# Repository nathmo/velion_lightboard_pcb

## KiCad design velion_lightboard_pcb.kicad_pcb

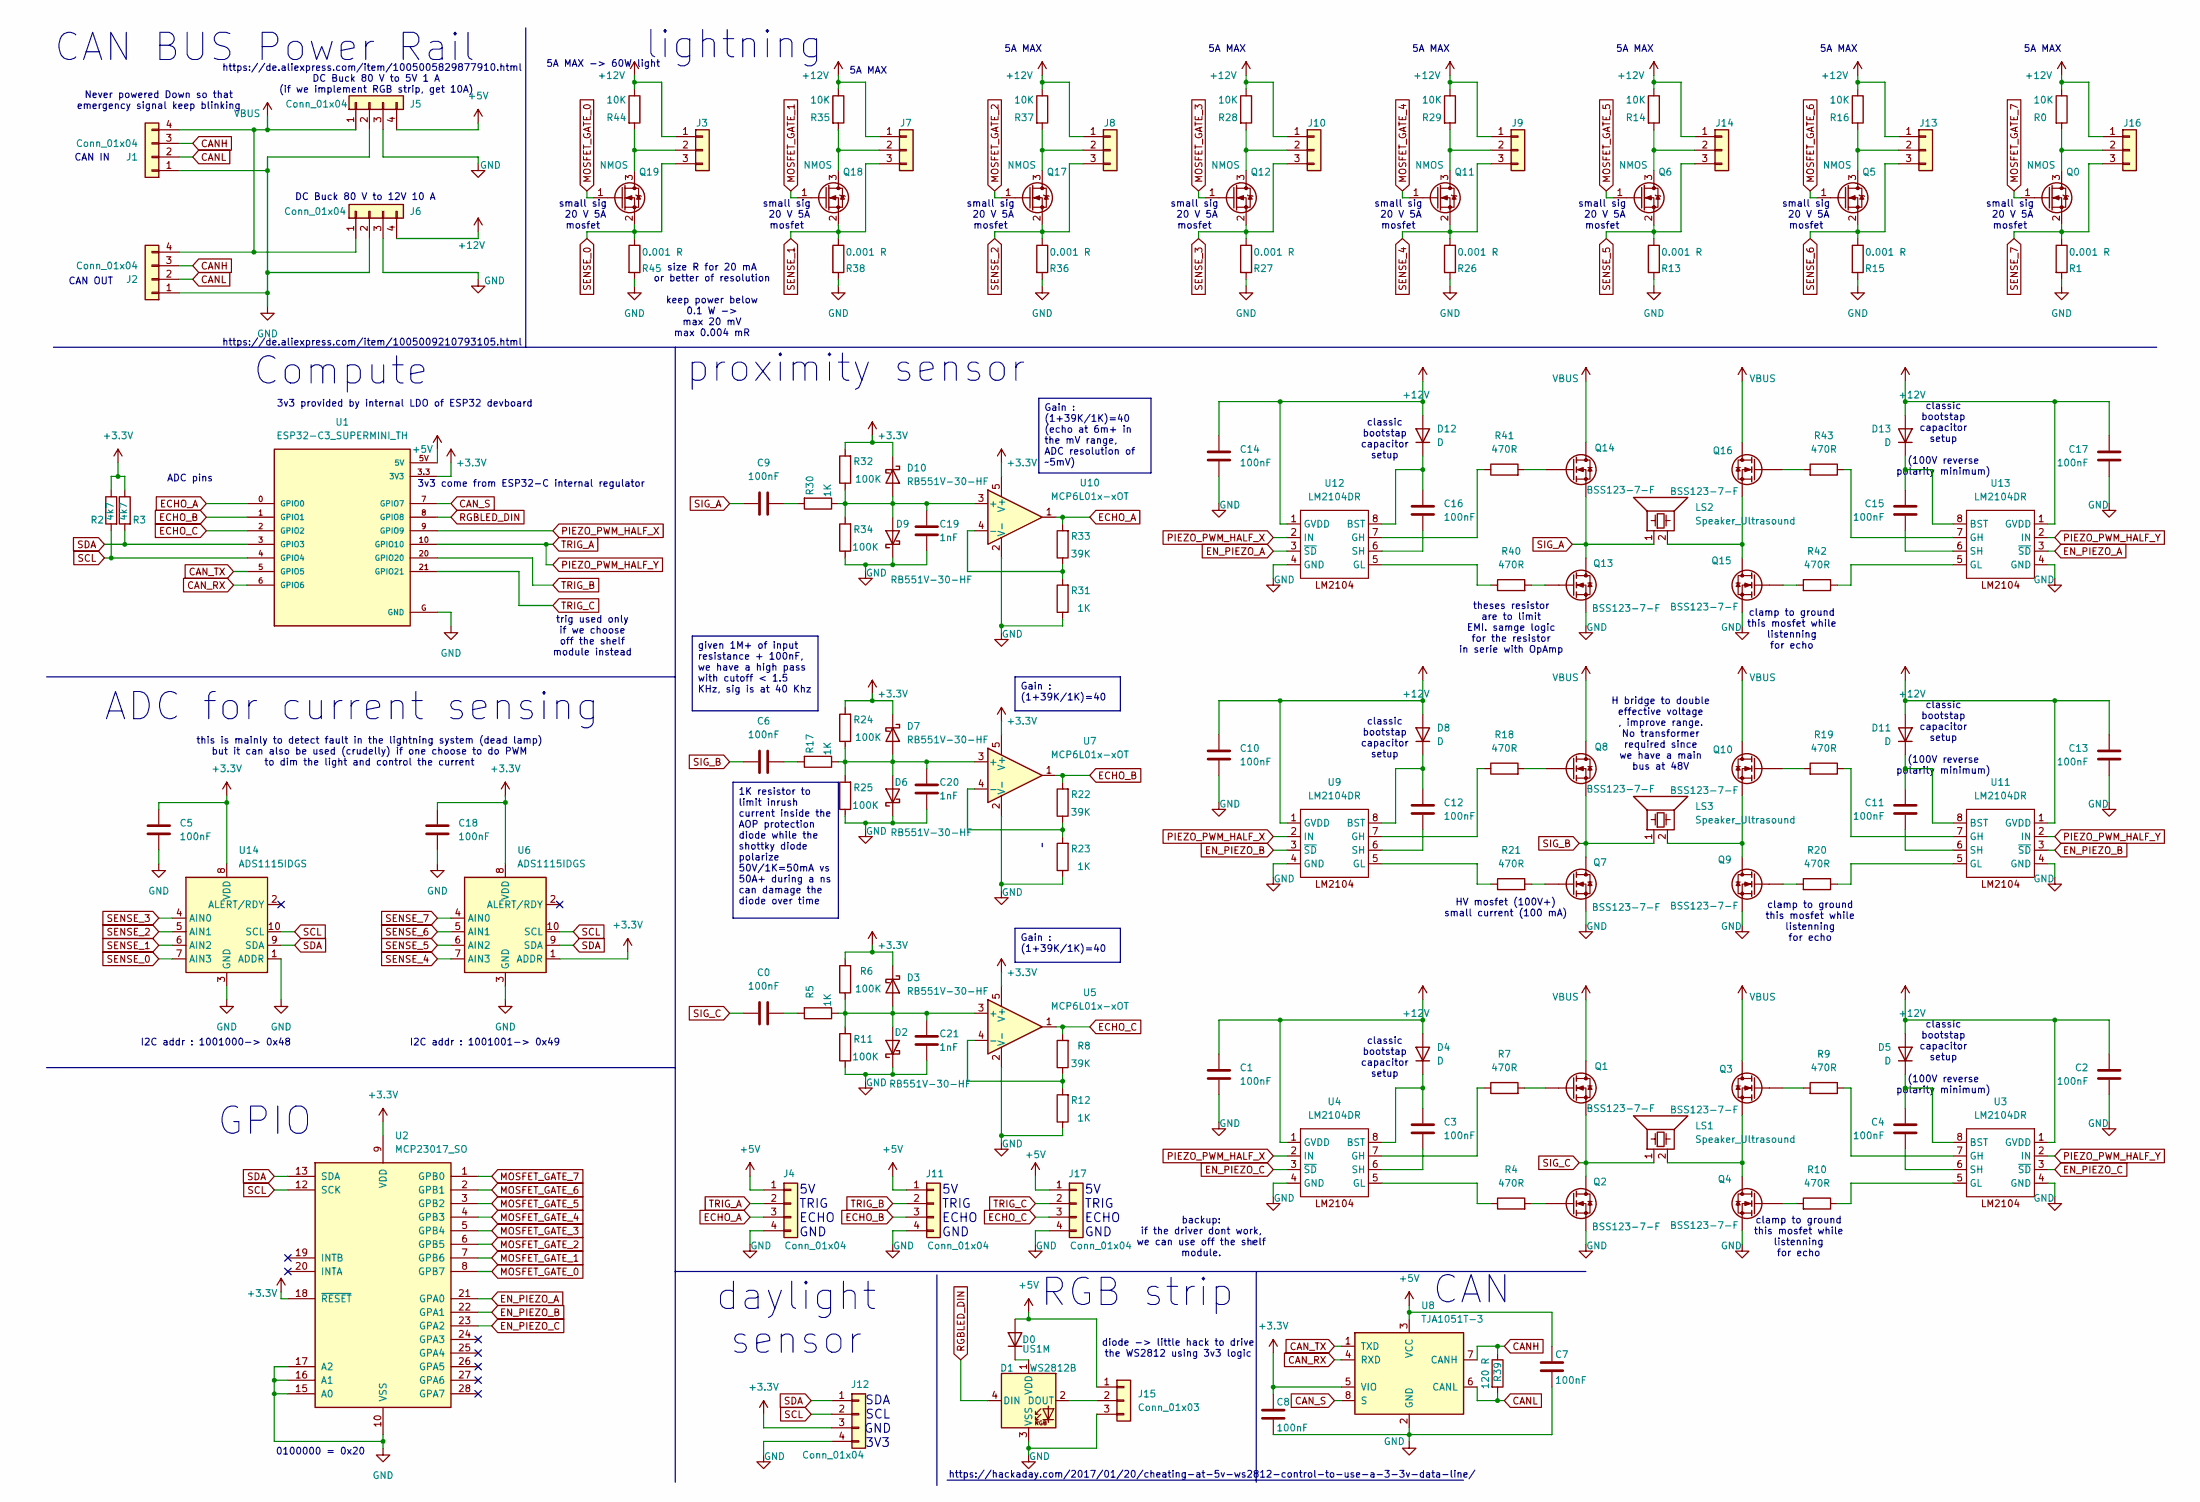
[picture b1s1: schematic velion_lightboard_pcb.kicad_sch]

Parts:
C0, C1, C2, C3, C4, C5, C6, C7, C8, C9, C10, C11, C12, C13, C14, C15, C16, C17, C18: 100nF; C_1206_3216Metric_Pad1.33x1.80mm_HandSolder
C19, C20, C21: 1nF; C_1206_3216Metric_Pad1.33x1.80mm_HandSolder
D0: US1M; D_SMA
D1: WS2812B; LED_WS2812B_PLCC4_5.0x5.0mm_P3.2mm
D2, D3, D6, D7, D9, D10: RB551V-30-HF; D_SOD-323_HandSoldering
D4, D5, D8, D11, D12, D13: D; D_SMA
J1, J2, J5, J6, J12: Conn_01x04; 15EDG-4P
J3, J7, J8, J9, J10, J13, J14, J15, J16: Conn_01x03; 15EDG-3P
J4, J11, J17: Conn_01x04; PinHeader_1x04_P2.54mm_Vertical
LS1, LS2, LS3: Speaker_Ultrasound; 15EDG-2P
Q0, Q5, Q6, Q11, Q12, Q17, Q18, Q19: NMOS; SOT-23
Q1, Q2, Q3, Q4, Q7, Q8, Q9, Q10, Q13, Q14, Q15, Q16: BSS123-7-F; BSS123_TSOT-23_HandSoldering
R0, R14, R16, R28, R29, R35, R37, R44: 10K; R_1206_3216Metric_Pad1.30x1.75mm_HandSolder
R1, R13, R15, R26, R27, R36, R38, R45: 0.001 R; R_2512_6332Metric_Pad1.40x3.35mm_HandSolder
R2, R3: 4k7; R_1206_3216Metric_Pad1.30x1.75mm_HandSolder
R4, R7, R9, R10, R18, R19, R20, R21, R40, R41, R42, R43: 470R; R_1206_3216Metric_Pad1.30x1.75mm_HandSolder
R5, R12, R17, R23, R30, R31: 1K; R_1206_3216Metric_Pad1.30x1.75mm_HandSolder
R6, R11, R24, R25, R32, R34: 100K; R_1206_3216Metric_Pad1.30x1.75mm_HandSolder
R8, R22, R33: 39K; R_1206_3216Metric_Pad1.30x1.75mm_HandSolder
R39: 120 R; R_1206_3216Metric_Pad1.30x1.75mm_HandSolder
U1: ESP32-C3_SUPERMINI_TH; MODULE_ESP32-C3_SUPERMINI_TH
U2: MCP23017_SO; SOIC-28W_7.5x17.9mm_P1.27mm
U3, U4, U9, U11, U12, U13: LM2104DR; SO-8_3.9x4.9mm_P1.27mm
U5, U7, U10: MCP6L01x-xOT; SOT-23-5
U6, U14: ADS1115IDGS; VSSOP-10_3x3mm_P0.5mm
U8: TJA1051T-3; SOIC-8_3.9x4.9mm_P1.27mm

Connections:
+3.3V: C5.1, C8.1, C18.1, D3.1 (K), D7.1 (K), D10.1 (K), J12.3, R2.1, R3.1, R6.2, R24.2, R32.2, U1.3.3 (3V3), U2.9 (VDD), U2.18 (~RESET), U5.5 (V+), U6.1 (ADDR), U6.8 (VDD), U7.5 (V+), U8.5 (VIO), U10.5 (V+), U14.8 (VDD)
+5V: C7.1, D0.2 (A), J4.1, J5.4, J11.1, J15.1, J17.1, U1.5V, U8.3 (VCC)
+12V: C1.1, C2.1, C10.1, C13.1, C14.1, C17.1, D4.2 (A), D5.2 (A), D8.2 (A), D11.2 (A), D12.2 (A), D13.2 (A), J3.1, J6.4, J7.1, J8.1, J9.1, J10.1, J13.1, J14.1, J16.1, R0.1, R14.1, R16.1, R28.1, R29.1, R35.1, R37.1, R44.1, U3.1 (GVDD), U4.1 (GVDD), U9.1 (GVDD), U11.1 (GVDD), U12.1 (GVDD), U13.1 (GVDD)
CANH: J1.3, J2.3, R39.1, U8.7 (CANH)
CANL: J1.2, J2.2, R39.2, U8.6 (CANL)
CAN_RX: U1.6 (GPIO6), U8.4 (RXD)
CAN_S: U1.7 (GPIO7), U8.8 (S)
CAN_TX: U1.5 (GPIO5), U8.1 (TXD)
ECHO_A: J4.3, R33.2, U1.0 (GPIO0), U10.1
ECHO_B: J11.3, R22.2, U1.1 (GPIO1), U7.1
ECHO_C: J17.3, R8.2, U1.2 (GPIO2), U5.1
EN_PIEZO_A: U2.21 (GPA0), U12.3 (~SD), U13.3 (~SD)
EN_PIEZO_B: U2.22 (GPA1), U9.3 (~SD), U11.3 (~SD)
EN_PIEZO_C: U2.23 (GPA2), U3.3 (~SD), U4.3 (~SD)
GND: C1.2, C2.2, C5.2, C7.2, C8.2, C10.2, C13.2, C14.2, C17.2, C18.2, C19.1, C20.1, C21.1, D1.3 (VSS), D2.1 (K), D6.1 (K), D9.1 (K), J1.1, J2.1, J4.4, J5.2, J5.3, J6.2, J6.3, J11.4, J12.4, J15.3, J17.4, Q2.S, Q4.S, Q7.S, Q9.S, Q13.S, Q15.S, R1.2, R11.1, R12.1, R13.2, R15.2, R23.1, R25.1, R26.2, R27.2, R31.1, R34.1, R36.2, R38.2, R45.2, U1.G (GND), U2.10 (VSS), U2.15 (A0), U2.16 (A1), U2.17 (A2), U3.4 (GND), U4.4 (GND), U5.2 (V-), U6.3 (GND), U7.2 (V-), U8.2 (GND), U9.4 (GND), U10.2 (V-), U11.4 (GND), U12.4 (GND), U13.4 (GND), U14.1 (ADDR), U14.3 (GND)
MOSFET_GATE_0: Q19.1 (G), U2.8 (GPB7)
MOSFET_GATE_1: Q18.1 (G), U2.7 (GPB6)
MOSFET_GATE_2: Q17.1 (G), U2.6 (GPB5)
MOSFET_GATE_3: Q12.1 (G), U2.5 (GPB4)
MOSFET_GATE_4: Q11.1 (G), U2.4 (GPB3)
MOSFET_GATE_5: Q6.1 (G), U2.3 (GPB2)
MOSFET_GATE_6: Q5.1 (G), U2.2 (GPB1)
MOSFET_GATE_7: Q0.1 (G), U2.1 (GPB0)
unnamed: C0.1, R5.2
unnamed: C6.1, R17.2
unnamed: C9.1, R30.2
unnamed: D0.1 (K), D1.1 (VDD)
unnamed: D1.2 (DOUT), J15.2
unnamed: C21.2, D2.2 (A), D3.2 (A), R5.1, R6.1, R11.2, U5.3 (+)
unnamed: C3.1, D4.1 (K), U4.8 (BST)
unnamed: C4.1, D5.1 (K), U3.8 (BST)
unnamed: C20.2, D6.2 (A), D7.2 (A), R17.1, R24.1, R25.2, U7.3 (+)
unnamed: C12.1, D8.1 (K), U9.8 (BST)
unnamed: C19.2, D9.2 (A), D10.2 (A), R30.1, R32.1, R34.2, U10.3 (+)
unnamed: C11.1, D11.1 (K), U11.8 (BST)
unnamed: C16.1, D12.1 (K), U12.8 (BST)
unnamed: C15.1, D13.1 (K), U13.8 (BST)
unnamed: J3.2, Q19.3 (D), R44.2
unnamed: J7.2, Q18.3 (D), R35.2
unnamed: J8.2, Q17.3 (D), R37.2
unnamed: J9.2, Q11.3 (D), R29.2
unnamed: J10.2, Q12.3 (D), R28.2
unnamed: J13.2, Q5.3 (D), R16.2
unnamed: J14.2, Q6.3 (D), R14.2
unnamed: J16.2, Q0.3 (D), R0.2
unnamed: LS1.2, Q3.S, Q4.D
unnamed: LS2.2, Q15.D, Q16.S
unnamed: LS3.2, Q9.D, Q10.S
unnamed: Q1.G, R7.2
unnamed: Q2.G, R4.2
unnamed: Q3.G, R9.2
unnamed: Q4.G, R10.2
unnamed: Q7.G, R21.2
unnamed: Q8.G, R18.2
unnamed: Q9.G, R20.2
unnamed: Q10.G, R19.2
unnamed: Q13.G, R40.2
unnamed: Q14.G, R41.2
unnamed: Q15.G, R42.2
unnamed: Q16.G, R43.2
unnamed: R9.1, U3.7 (GH)
unnamed: R10.1, U3.5 (GL)
unnamed: C4.2, U3.6 (SH)
unnamed: R7.1, U4.7 (GH)
unnamed: R4.1, U4.5 (GL)
unnamed: C3.2, U4.6 (SH)
unnamed: R8.1, R12.2, U5.4 (-)
unnamed: R22.1, R23.2, U7.4 (-)
unnamed: R18.1, U9.7 (GH)
unnamed: R21.1, U9.5 (GL)
unnamed: C12.2, U9.6 (SH)
unnamed: R31.2, R33.1, U10.4 (-)
unnamed: R19.1, U11.7 (GH)
unnamed: R20.1, U11.5 (GL)
unnamed: C11.2, U11.6 (SH)
unnamed: R41.1, U12.7 (GH)
unnamed: R40.1, U12.5 (GL)
unnamed: C16.2, U12.6 (SH)
unnamed: R43.1, U13.7 (GH)
unnamed: R42.1, U13.5 (GL)
unnamed: C15.2, U13.6 (SH)
PIEZO_PWM_HALF_X: U1.9 (GPIO9), U4.2 (IN), U9.2 (IN), U12.2 (IN)
PIEZO_PWM_HALF_Y: J4.2, U1.10 (GPIO10), U3.2 (IN), U11.2 (IN), U13.2 (IN)
RGBLED_DIN: D1.4 (DIN), U1.8 (GPIO8)
SCL: J12.2, R2.2, U1.4 (GPIO4), U2.12 (SCK), U6.10 (SCL), U14.10 (SCL)
SDA: J12.1, R3.2, U1.3 (GPIO3), U2.13 (SDA), U6.9 (SDA), U14.9 (SDA)
SENSE_0: J3.3, Q19.2 (S), R45.1, U14.7 (AIN3)
SENSE_1: J7.3, Q18.2 (S), R38.1, U14.6 (AIN2)
SENSE_2: J8.3, Q17.2 (S), R36.1, U14.5 (AIN1)
SENSE_3: J10.3, Q12.2 (S), R27.1, U14.4 (AIN0)
SENSE_4: J9.3, Q11.2 (S), R26.1, U6.7 (AIN3)
SENSE_5: J14.3, Q6.2 (S), R13.1, U6.6 (AIN2)
SENSE_6: J13.3, Q5.2 (S), R15.1, U6.5 (AIN1)
SENSE_7: J16.3, Q0.2 (S), R1.1, U6.4 (AIN0)
SIG_A: C9.2, LS2.1, Q13.D, Q14.S
SIG_B: C6.2, LS3.1, Q7.D, Q8.S
SIG_C: C0.2, LS1.1, Q1.S, Q2.D
TRIG_B: J11.2, U1.20 (GPIO20)
TRIG_C: J17.2, U1.21 (GPIO21)
VBUS: J1.4, J2.4, J5.1, J6.1, Q1.D, Q3.D, Q8.D, Q10.D, Q14.D, Q16.D

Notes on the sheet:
5A MAX
small sig 20 V 5A mosfet
CAN OUT
classic bootstap capacitor setup
Compute
I2C addr : 1001001-> 0x49
GPIO
RGB strip
clamp to ground this mosfet while listenning for echo
CAN IN
this is mainly to detect fault in the lightning system (dead lamp) but it can also be used (crudelly) if one choose to do PWM to dim the light and control the current
classic bootstap capacitor setup (100V reverse polarity minimum)
lightning
0100000 = 0x20
Never powered Down so that emergency signal keep blinking
5V TRIG ECHO GND
https://de.aliexpress.com/item/1005009210793105.html
trig used only if we choose off the shelf module instead
ADC pins
proximity sensor
theses resistor are to limit EMI. samge logic for the resistor in serie with OpAmp
DC Buck 80 V to 12V 10 A
3v3 provided by internal LDO of ESP32 devboard
backup: if the driver dont work, we can use off the shelf module.
daylight sensor
size R for 20 mA or better of resolution keep power below 0.1 W -> max 20 mV max 0.004 mR
DC Buck 80 V to 5V 1 A (if we implement RGB strip, get 10A)
ADC for current sensing
I2C addr : 1001000-> 0x48
H bridge to double effective voltage , improve range. No transformer required since we have a main bus at 48V
5A MAX -> 60W light
CAN
diode -> little hack to drive the WS2812 using 3v3 logic
https://de.aliexpress.com/item/1005005829877910.html
CAN BUS Power Rail
https://hackaday.com/2017/01/20/cheating-at-5v-ws2812-control-to-use-a-3-3v-data-line/
3v3 come from ESP32-C internal regulator
SDA SCL GND 3V3
HV mosfet (100V+) small current (100 mA)
Gain : (1+39K/1K)=40

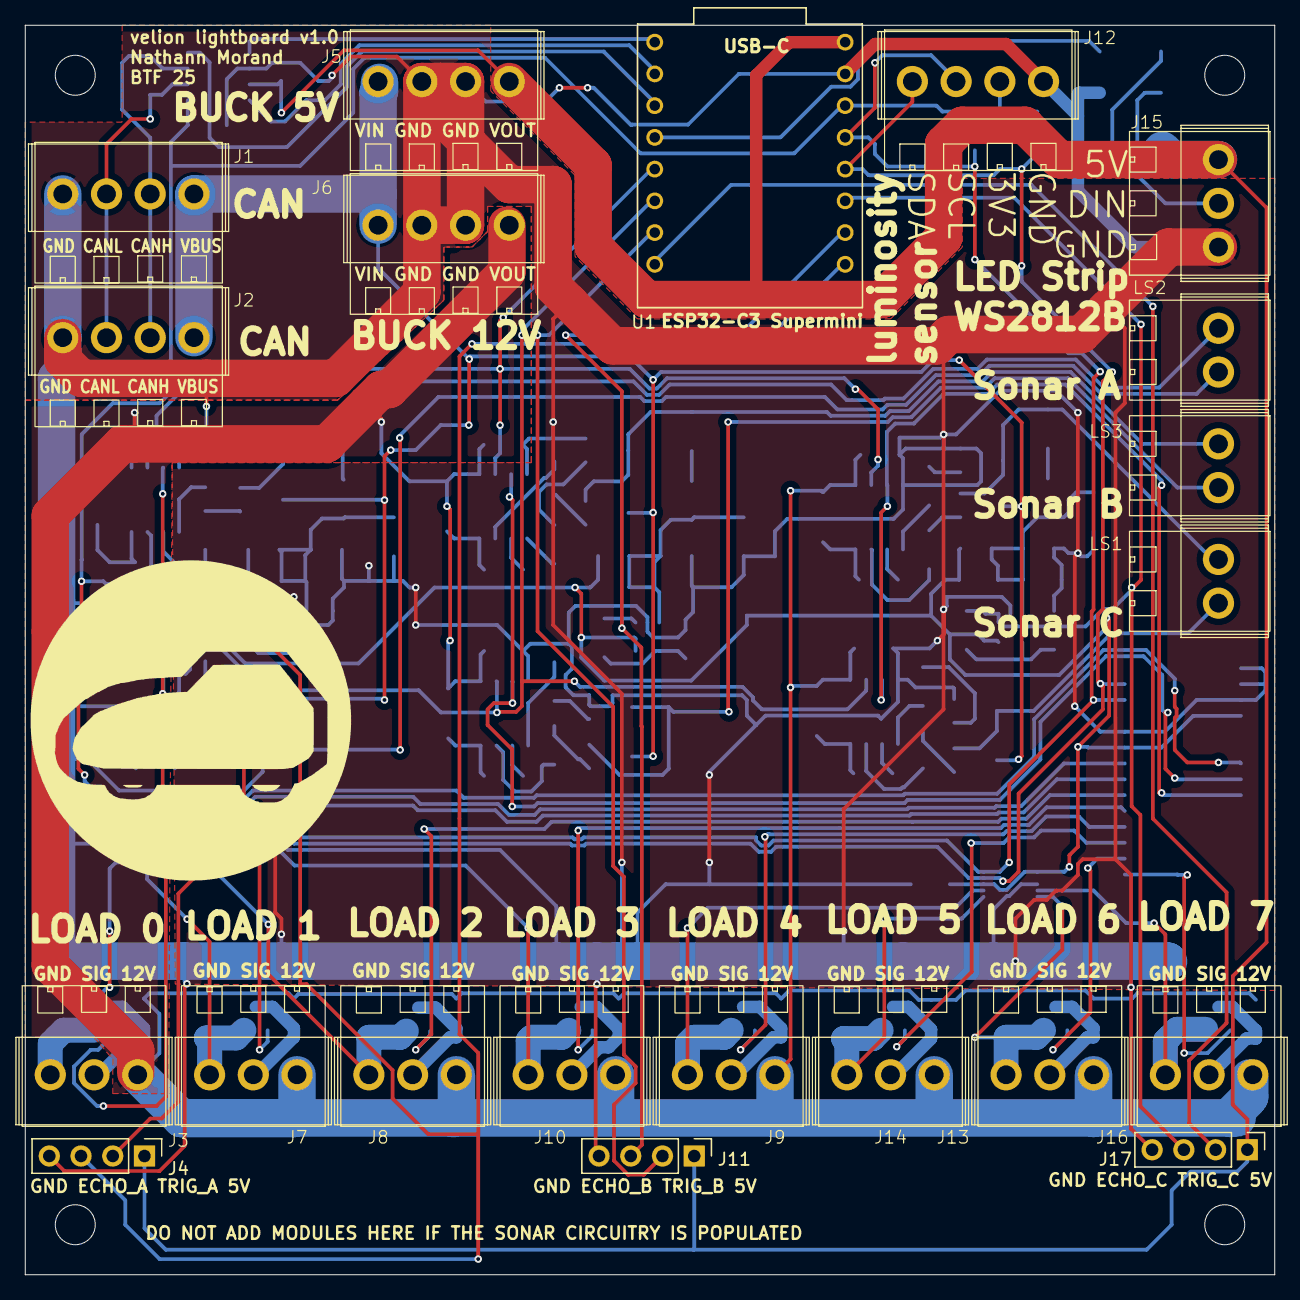
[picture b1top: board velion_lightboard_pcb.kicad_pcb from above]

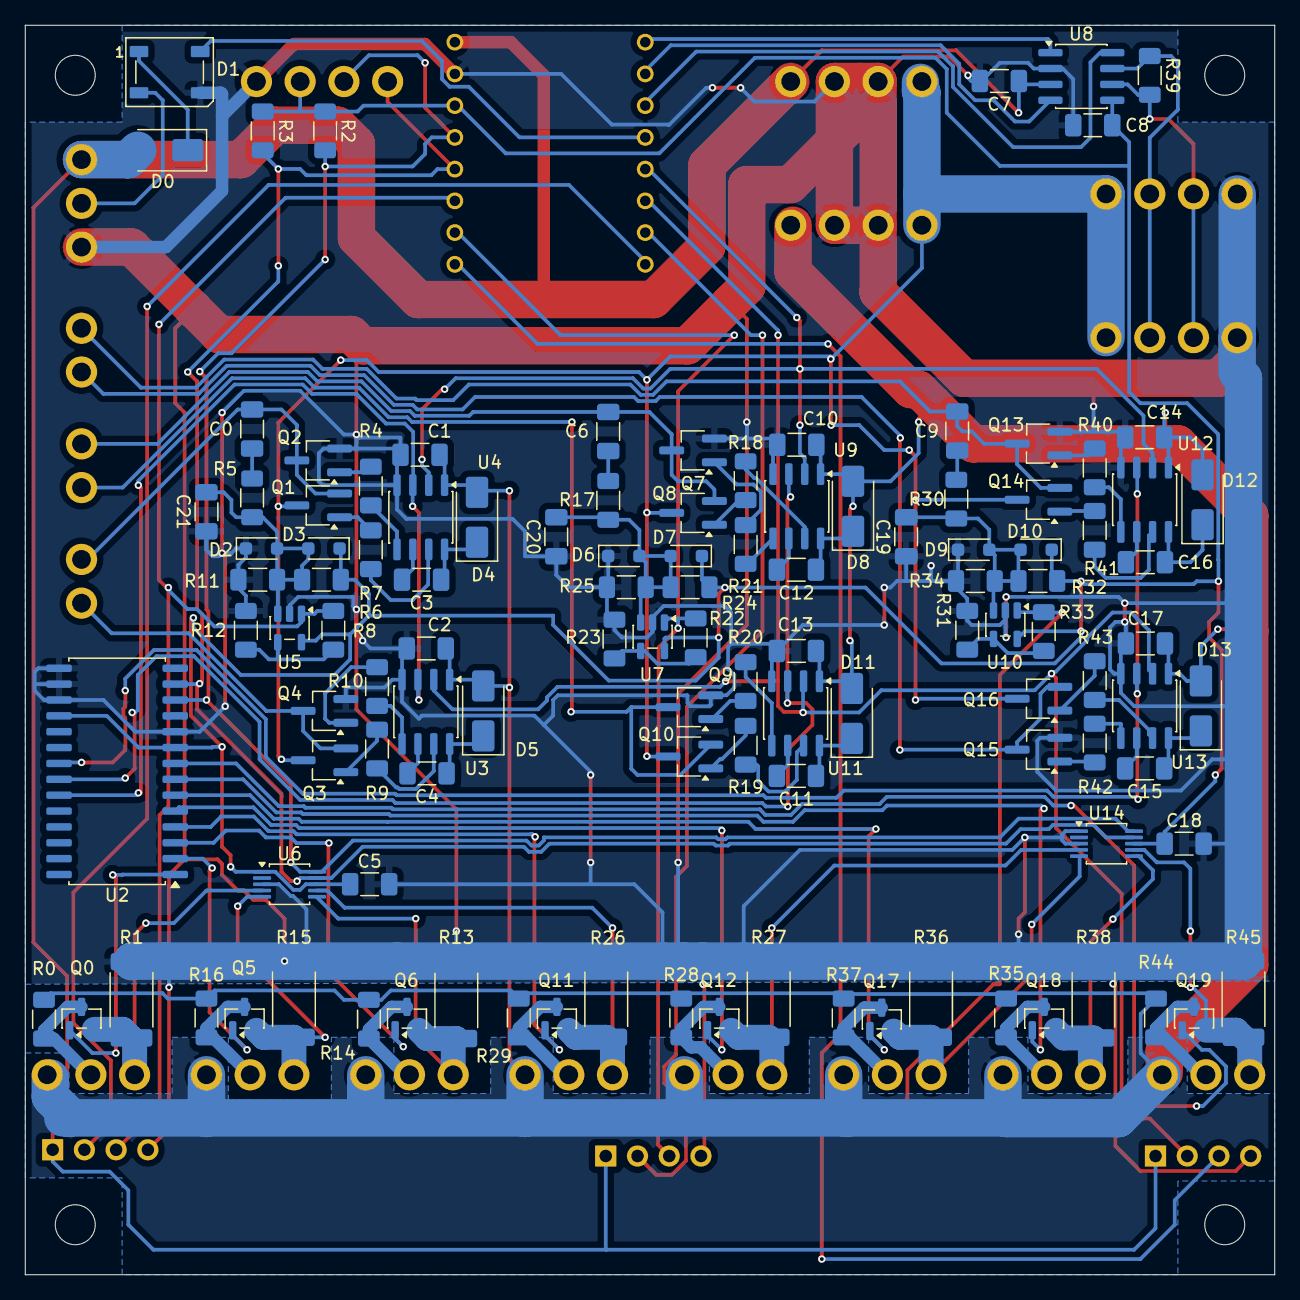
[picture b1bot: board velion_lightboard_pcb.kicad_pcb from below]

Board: 2 copper layers, 100.0 x 100.0 mm, 140 parts (115 on the bottom side), 100 nets.

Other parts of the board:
TR1, TR2, TR3, TR4: MountingHole_3.2mm_M3

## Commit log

2025-12-27 added library
2025-12-27 removed stray file
2025-12-28 designing relay board
2025-12-28 rotated image
2025-12-28 Auto-export KiCad PDFs
2025-12-29 switched MCU, implemented led driver, TODO : rangerfinder
2025-12-30 Implemented piezo sonar driver
2025-12-30 implemented Analog stage for piezzo sonar
2025-12-31 layaing out the components
2026-01-01 routed the PCB, need review
2026-01-05 generated fab file, added capacitor for low pass/antialiasing in Sonar
2026-01-05 replaced the light sensor pin header by a standard bornier
2026-01-05 adding BOM for mouser
